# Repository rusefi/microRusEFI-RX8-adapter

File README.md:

# proteus-RX8-adapter

Easy to solder breakout board for https://github.com/mck1117/proteus to meet 
[RX8 2004](https://github.com/rusefi/rusefi/wiki/Mazda-RX8-2004) 
[RX8 2005](https://github.com/rusefi/rusefi/wiki/Mazda-RX8-2005)
[RX8 2007](https://github.com/rusefi/rusefi/wiki/Mazda-RX8-2007)

Pinout sheet https://docs.google.com/spreadsheets/d/1tTa7E6qxEAyikSSsWZ_wzRw9r-D-QrcE4l8kYaQWnQA

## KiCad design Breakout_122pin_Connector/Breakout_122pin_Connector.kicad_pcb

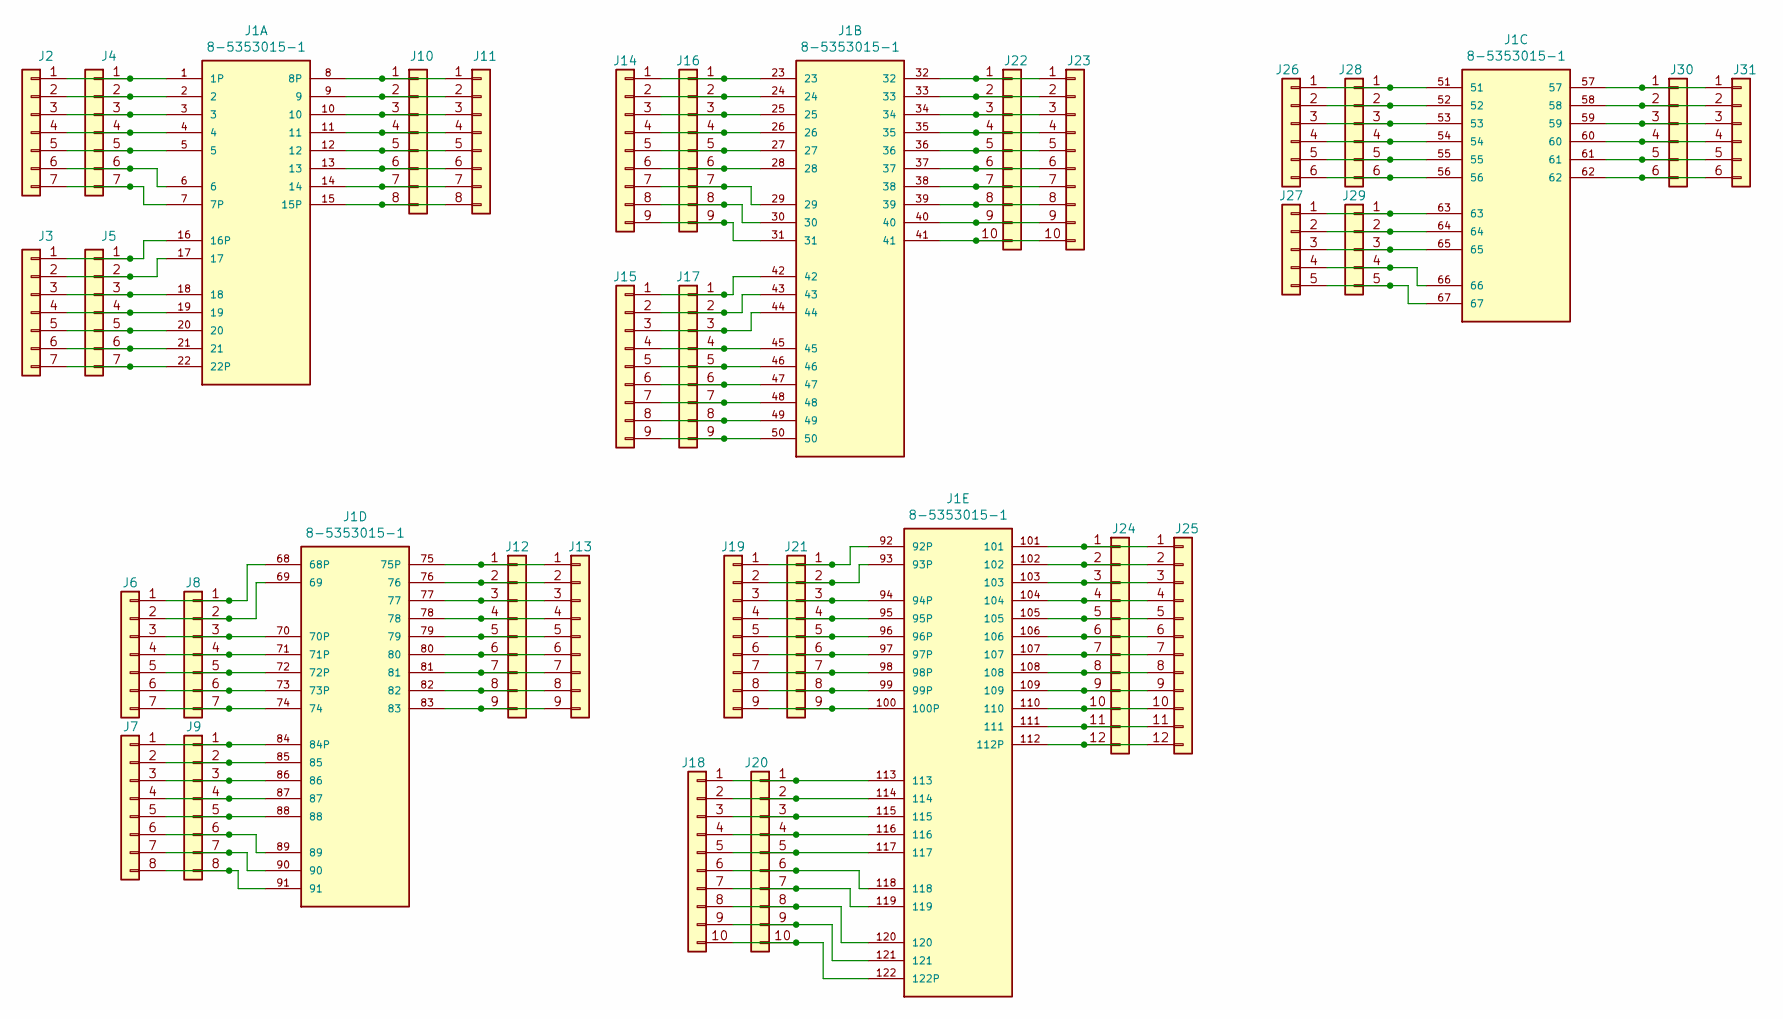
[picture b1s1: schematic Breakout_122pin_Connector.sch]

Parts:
J1: 8-5353015-1; TE_8-5353015-1
J2, J3, J4, J5, J6, J8: Conn_01x07; Pin_Header_Straight_1x07_Pitch2.54mm_big
J7, J9, J10, J11: Conn_01x08; Pin_Header_Straight_1x08_Pitch2.54mm_big
J12, J13, J14, J15, J16, J17, J19, J21: Conn_01x09; Pin_Header_Straight_1x09_Pitch2.54mm_big
J18, J20, J22, J23: Conn_01x10; Pin_Header_Straight_1x10_Pitch2.54mm_big
J24, J25: Conn_01x12; Pin_Header_Straight_1x12_Pitch2.54mm_big
J26, J28, J30, J31: Conn_01x06; Pin_Header_Straight_1x06_Pitch2.54mm_big
J27, J29: Conn_01x05; Pin_Header_Straight_1x05_Pitch2.54mm_big

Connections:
unnamed: J1.1 (1P), J2.1, J4.1
unnamed: J1.2, J2.2, J4.2
unnamed: J1.3, J2.3, J4.3
unnamed: J1.4, J2.4, J4.4
unnamed: J1.5, J2.5, J4.5
unnamed: J1.6, J2.6, J4.6
unnamed: J1.7 (7P), J2.7, J4.7
unnamed: J1.8 (8P), J10.1, J11.1
unnamed: J1.9, J10.2, J11.2
unnamed: J1.10, J10.3, J11.3
unnamed: J1.11, J10.4, J11.4
unnamed: J1.12, J10.5, J11.5
unnamed: J1.13, J10.6, J11.6
unnamed: J1.14, J10.7, J11.7
unnamed: J1.15 (15P), J10.8, J11.8
unnamed: J1.16 (16P), J3.1, J5.1
unnamed: J1.17, J3.2, J5.2
unnamed: J1.18, J3.3, J5.3
unnamed: J1.19, J3.4, J5.4
unnamed: J1.20, J3.5, J5.5
unnamed: J1.21, J3.6, J5.6
unnamed: J1.22 (22P), J3.7, J5.7
unnamed: J1.23, J14.1, J16.1
unnamed: J1.24, J14.2, J16.2
unnamed: J1.25, J14.3, J16.3
unnamed: J1.26, J14.4, J16.4
unnamed: J1.27, J14.5, J16.5
unnamed: J1.28, J14.6, J16.6
unnamed: J1.29, J14.7, J16.7
unnamed: J1.30, J14.8, J16.8
unnamed: J1.31, J14.9, J16.9
unnamed: J1.32, J22.1, J23.1
unnamed: J1.33, J22.2, J23.2
unnamed: J1.34, J22.3, J23.3
unnamed: J1.35, J22.4, J23.4
unnamed: J1.36, J22.5, J23.5
unnamed: J1.37, J22.6, J23.6
unnamed: J1.38, J22.7, J23.7
unnamed: J1.39, J22.8, J23.8
unnamed: J1.40, J22.9, J23.9
unnamed: J1.41, J22.10, J23.10
unnamed: J1.42, J15.1, J17.1
unnamed: J1.43, J15.2, J17.2
unnamed: J1.44, J15.3, J17.3
unnamed: J1.45, J15.4, J17.4
unnamed: J1.46, J15.5, J17.5
unnamed: J1.47, J15.6, J17.6
unnamed: J1.48, J15.7, J17.7
unnamed: J1.49, J15.8, J17.8
unnamed: J1.50, J15.9, J17.9
unnamed: J1.51, J26.1, J28.1
unnamed: J1.52, J26.2, J28.2
unnamed: J1.53, J26.3, J28.3
unnamed: J1.54, J26.4, J28.4
unnamed: J1.55, J26.5, J28.5
unnamed: J1.56, J26.6, J28.6
unnamed: J1.57, J30.1, J31.1
unnamed: J1.58, J30.2, J31.2
unnamed: J1.59, J30.3, J31.3
unnamed: J1.60, J30.4, J31.4
unnamed: J1.61, J30.5, J31.5
unnamed: J1.62, J30.6, J31.6
unnamed: J1.63, J27.1, J29.1
unnamed: J1.64, J27.2, J29.2
unnamed: J1.65, J27.3, J29.3
unnamed: J1.66, J27.4, J29.4
unnamed: J1.67, J27.5, J29.5
unnamed: J1.68 (68P), J6.1, J8.1
unnamed: J1.69, J6.2, J8.2
unnamed: J1.70 (70P), J6.3, J8.3
unnamed: J1.71 (71P), J6.4, J8.4
unnamed: J1.72 (72P), J6.5, J8.5
unnamed: J1.73 (73P), J6.6, J8.6
unnamed: J1.74, J6.7, J8.7
unnamed: J1.75 (75P), J12.1, J13.1
unnamed: J1.76, J12.2, J13.2
unnamed: J1.77, J12.3, J13.3
unnamed: J1.78, J12.4, J13.4
unnamed: J1.79, J12.5, J13.5
unnamed: J1.80, J12.6, J13.6
unnamed: J1.81, J12.7, J13.7
unnamed: J1.82, J12.8, J13.8
unnamed: J1.83, J12.9, J13.9
unnamed: J1.84 (84P), J7.1, J9.1
unnamed: J1.85, J7.2, J9.2
unnamed: J1.86, J7.3, J9.3
unnamed: J1.87, J7.4, J9.4
unnamed: J1.88, J7.5, J9.5
unnamed: J1.89, J7.6, J9.6
unnamed: J1.90, J7.7, J9.7
unnamed: J1.91, J7.8, J9.8
unnamed: J1.92 (92P), J19.1, J21.1
unnamed: J1.93 (93P), J19.2, J21.2
unnamed: J1.94 (94P), J19.3, J21.3
unnamed: J1.95 (95P), J19.4, J21.4
unnamed: J1.96 (96P), J19.5, J21.5
unnamed: J1.97 (97P), J19.6, J21.6
unnamed: J1.98 (98P), J19.7, J21.7
unnamed: J1.99 (99P), J19.8, J21.8
unnamed: J1.100 (100P), J19.9, J21.9
unnamed: J1.101, J24.1, J25.1
unnamed: J1.102, J24.2, J25.2
unnamed: J1.103, J24.3, J25.3
unnamed: J1.104, J24.4, J25.4
unnamed: J1.105, J24.5, J25.5
unnamed: J1.106, J24.6, J25.6
unnamed: J1.107, J24.7, J25.7
unnamed: J1.108, J24.8, J25.8
unnamed: J1.109, J24.9, J25.9
unnamed: J1.110, J24.10, J25.10
unnamed: J1.111, J24.11, J25.11
unnamed: J1.112 (112P), J24.12, J25.12
unnamed: J1.113, J18.1, J20.1
unnamed: J1.114, J18.2, J20.2
unnamed: J1.115, J18.3, J20.3
unnamed: J1.116, J18.4, J20.4
unnamed: J1.117, J18.5, J20.5
unnamed: J1.118, J18.6, J20.6
unnamed: J1.119, J18.7, J20.7
unnamed: J1.120, J18.8, J20.8
unnamed: J1.121, J18.9, J20.9
unnamed: J1.122 (122P), J18.10, J20.10

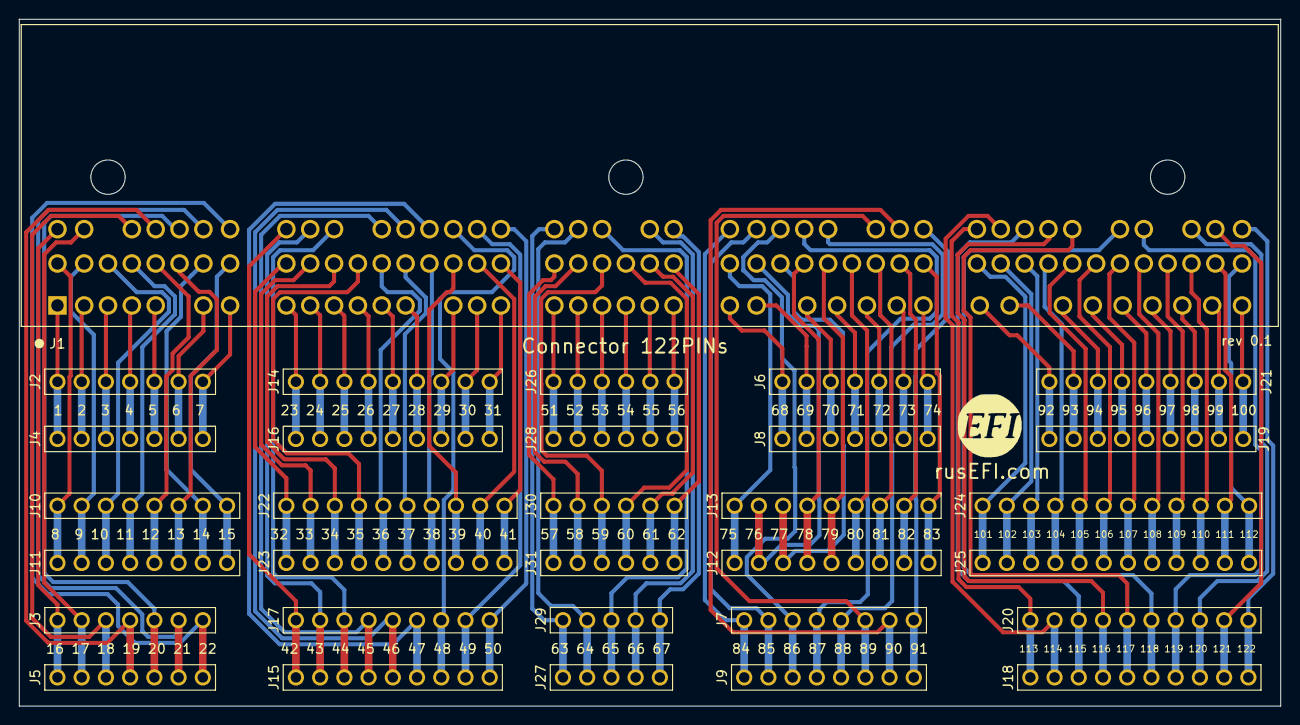
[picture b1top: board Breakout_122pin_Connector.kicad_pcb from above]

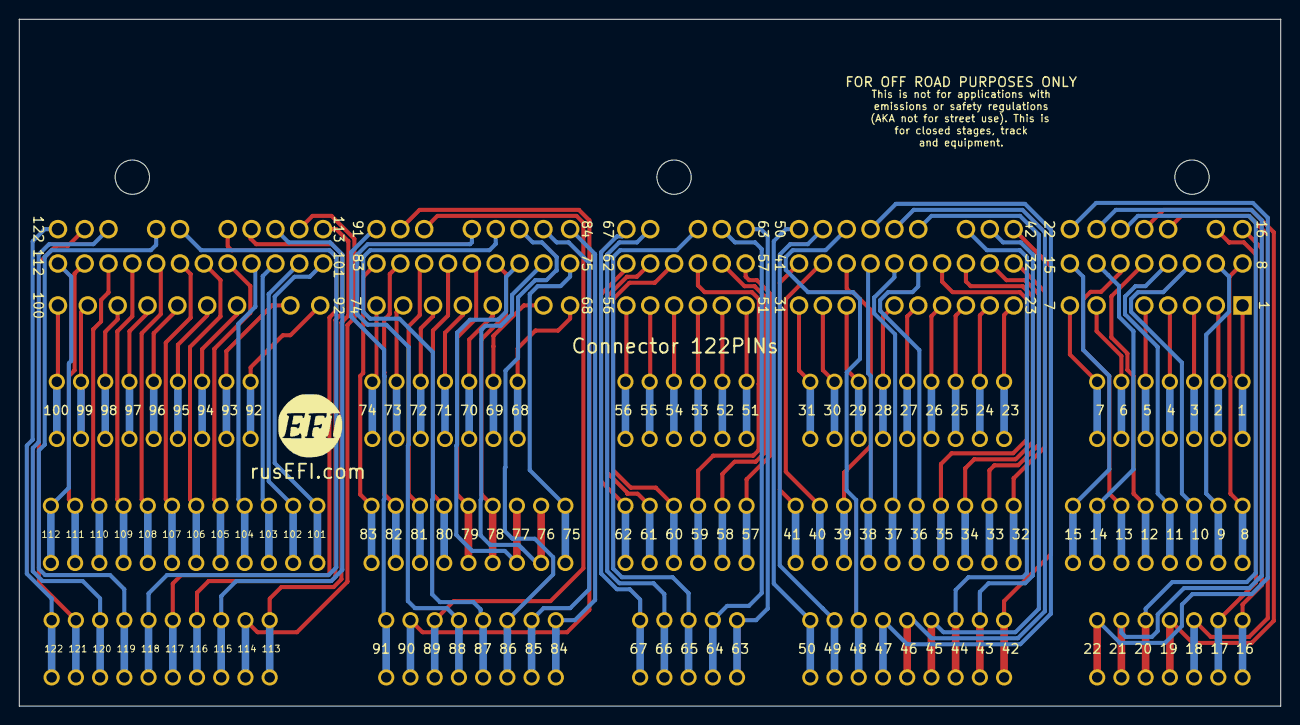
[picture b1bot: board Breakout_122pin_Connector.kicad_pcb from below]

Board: 2 copper layers, 132.2 x 72.0 mm, 34 parts (2 on the bottom side), 122 nets.

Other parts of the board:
G?: Disclaimer; Off_Road_Disclaimer
G?#2, G?#3: LOGO

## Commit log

2021-09-21 initial files
